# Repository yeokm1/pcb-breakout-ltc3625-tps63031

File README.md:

# pcb-breakout-ltc3625-tps63031
Pin breakout of the LTC3625 supercapacitor charger with TPS63031 3.3V regulator to through-hole pin headers for prototyping

<b>WARNING</b>: Consult the LTC3625 and TPS63031 datasheets in conjunction with the Eagle schematic to learn proper usage of this breakout.

If your project uses low currents it might be better enable power-save mode by setting the power save (PS) pin 7 of the TPS63031 to ground.

## PCB Design software and addons used

1. Eagle 7.5.0: I use Standard but Light should still be able to open/modify the files.
2. My custom ltc3625 library
3. [Seed-OPL-Connector](http://www.seeedstudio.com/wiki/File:OPL_eagle_library.zip)
4. [Coilcraft inductor](https://github.com/robertstarr/lbr_user/blob/master/inductor-coilcraft.lbr)
5. [TPS63031](http://e2e.ti.com/support/development_tools/webench_design_center/f/234/p/379556/1338022)

## Images
None at this time

##Schematic drawings
Images are exported from Eagle at 600dpi.

## Parts required
1. Linear Technology LTC3625
2. Texas Instruments TPS63031
3. 4x 10uF 0805 ceramic capacitors
4. 0.1uF 0805 ceramic capacitor
5. 2x 3.3uH DR73 inductors
6. 0805 resistor for LED
7. 0805 LED
8. 2x 8-pin through-hole pin headers
9. Hirose ZX62D-B-5PA8 micro-USB connector
10. 1.5uH inductor

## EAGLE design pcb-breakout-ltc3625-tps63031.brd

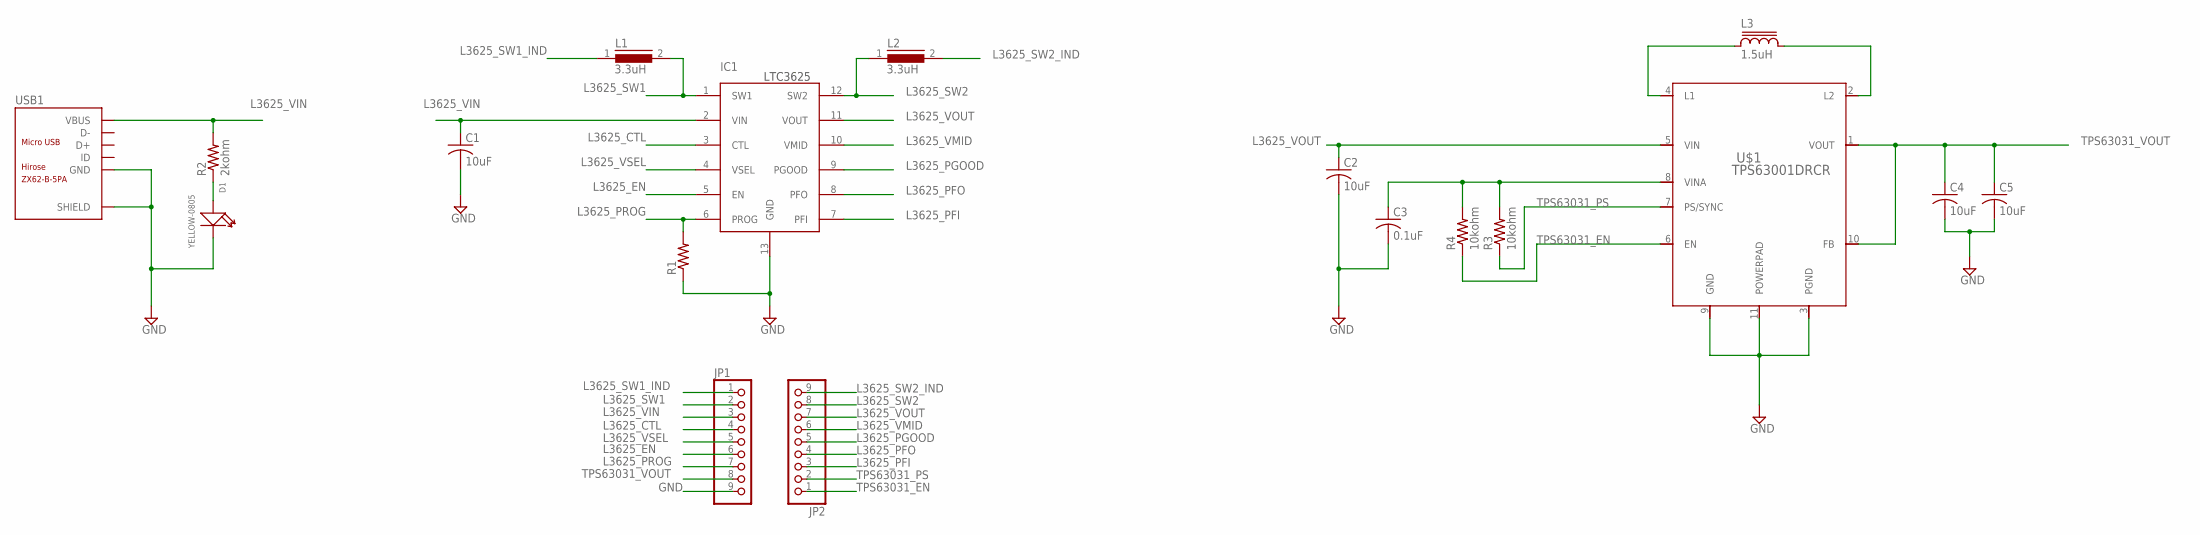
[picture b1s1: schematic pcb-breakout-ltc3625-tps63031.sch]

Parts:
C1, C2, C4, C5: 10uF; C0805
C3: 0.1uF; C0805
D1: YELLOW-0805; LED-0805
IC1: LTC3625EDE; DFN12(DE)
JP1, JP2: PINHD-1X9; 1X09
L1, L2: 3.3uH; DR73
L3: 1.5uH; LPS3015
R1: R-US_R0805; R0805
R2: 2kohm; R0805
R3, R4: 10kohm; R0805
U$1: TPS63001DRCR; NEWPVSON-N10
USB1: ZX62-B-5PA; MICRO-USB5+6P-SMD-0.65-AB

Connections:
GND: C1.2, C2.2, C3.2, C4.2, C5.2, D1.-, IC1.13 (GND), JP1.9, R1.1, U$1.3 (PGND), U$1.9 (GND), U$1.11 (POWERPAD), USB1.5 (GND), USB1.P1 (SHIELD), USB1.P2 (SHIELD), USB1.P3 (SHIELD), USB1.P4 (SHIELD), USB1.P5 (SHIELD), USB1.P6 (SHIELD)
L3625_CTL: IC1.3 (CTL), JP1.4
L3625_EN: IC1.5 (EN), JP1.6
L3625_PFI: IC1.7 (PFI), JP2.3
L3625_PFO: IC1.8 (PFO), JP2.4
L3625_PGOOD: IC1.9 (PGOOD), JP2.5
L3625_PROG: IC1.6 (PROG), JP1.7, R1.2
L3625_SW1: IC1.1 (SW1), JP1.2, L1.2
L3625_SW1_IND: JP1.1, L1.1
L3625_SW2: IC1.12 (SW2), JP2.8, L2.1
L3625_SW2_IND: JP2.9, L2.2
L3625_VIN: C1.1, IC1.2 (VIN), JP1.3, R2.2, USB1.1 (VBUS)
L3625_VMID: IC1.10 (VMID), JP2.6
L3625_VOUT: C2.1, IC1.11 (VOUT), JP2.7, U$1.5 (VIN)
L3625_VSEL: IC1.4 (VSEL), JP1.5
unnamed: L3.2, U$1.2 (L2)
unnamed: L3.1, U$1.4 (L1)
unnamed: D1.+, R2.1
unnamed: C3.1, R3.2, R4.2, U$1.8 (VINA)
TPS63031_EN: JP2.1, R4.1, U$1.6 (EN)
TPS63031_PS: JP2.2, R3.1, U$1.7 (PS/SYNC)
TPS63031_VOUT: C4.1, C5.1, JP1.8, U$1.1 (VOUT), U$1.10 (FB)

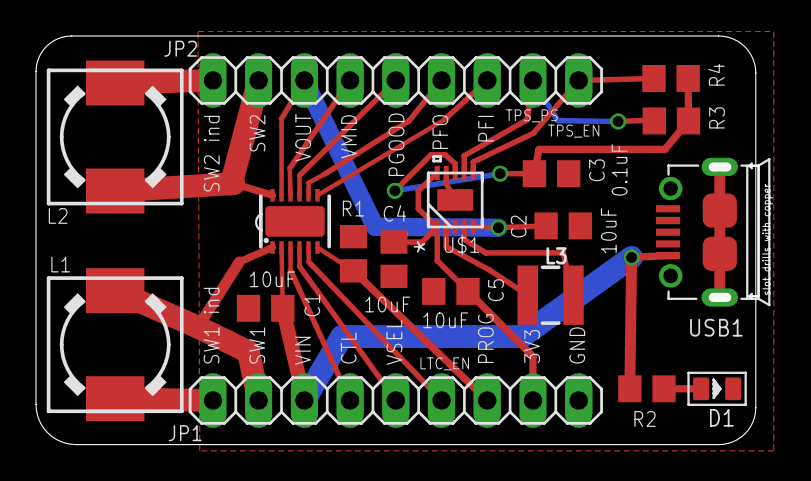
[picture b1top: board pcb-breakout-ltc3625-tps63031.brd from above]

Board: 2 copper layers, 40.0 x 22.7 mm, 18 parts (0 on the bottom side), 22 nets.

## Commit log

2016-01-29 Rev1 gerbers and images
2016-01-29 update to use newer ltc3625.lbr with device label
2016-02-11 Show 0.1uF label for C3 on tplace. Up rev number
2016-02-11 show all layers
2016-02-11 new board omg
2016-02-11 increase 3V3 trace width
2016-02-11 corrected package error in ltc3625 lbr
2016-02-11 2kohm for led resistor value
2016-02-11 adjust positioning
2016-02-11 Breakout pins TPS EN and PS and add pull up resistors to them
2016-02-11 add silkscreen for R3 and R4 description
2016-02-12 rev-2 gerbel
2016-07-06 add inductor to components in readme
2019-09-14 Space added to see headers
